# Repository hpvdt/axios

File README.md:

*This is the repository for our human powered submarine Axios, that we have decided to no longer to pursue. **IT IS NOT COMPLETE, LET ALONE TESTED.***

*Our motivation for making this repository public to to share what progress we did make to help others who might be interested in developing a similar system.*

# Axios

Our attempt at a human powered submarine, titled Axios. Within it there were two electronics systems to be implemented: rebreather monitoring and navigation. These were meant to be operate entirely independently of one another, being powered off separate batteries.

In this repository resides the code and hardware design files prepared for the initial versions of these systems from before the team decided to cancel the project.

Both systems were based around ATmega328P microcontrollers due to the team's familiarity with them and their adaquate amount of peripherals for serving both roles.

## Rebreather System

This was meant to supervise the different gas sensors around the submarine hull to inform the pilot about the atmospheric state within Axios. It collected data from three oxygen sensors and one carbon dioxide (CO2) sensor, it then displayed the value of each on separate seven-segment displays.

Of the two systems prepared for Axios, this was by far the more mature one. It was essentially ready for final deployment.

### Carbon Dioxide Sensing

For monitoring CO2 an MH-Z19 sensor was used which uses infrared to measure CO2 in the air. Getting data with the sensor was simple, it outputs a PWM signal at 1Hz that was trivial to monitor using the ATmega328P. The only hardware needed to interface it with the Arduino was a level shifting transistor to step the 3.3V PWM signal to 5V for the microcontroller to read.

One minor note we were unaware of is that the sensor has a small heater within it which is used to measure the CO2. This means the sensor occasionally draws a surge of current to keep it warm. This caused us to think the system was malfunctioning and drawing excessive power in our preliminary tests.

### Oxygen Sensing

This was the main focus of this board, since we were responsible for reading the raw sensor data. The oxygen sensors we were planning to use were standard oxygen sensors used for SCUBA diving. These are essentially chemical cells that when exposed to varying concentrations of oxygen in the air would vary their voltage proportionally. They had two issues the circuit needed to address:

1. The output voltage was pretty small. About 65mV for a new cell at 100% oxygen, but we would ideally be monitoring 21%, so about 20mV.
2. Although roughly linear, the output at 0% was not 0 mV, but about 15 mV.
3. Being chemical cells, they would gradually degrade and our circuit would need to be tuned for this.

The solution for this was a set of of high precision amplifiers made from operational amplifiers. These would buffer and then amplifier the sensor output to a level more easily read by the ATmega with its internal ADC resolution of about 4 mV. To adjust the circuit for the sensors as they aged we would conduct a two-point calibration (at 100% and 21% oxygen levels) adjusting potentiometers to get the display values to match these conditions.

## Navigation

Axios was designed to be controlled by three servo-actuated control fins. These needed a microcontroller to receive input from the captain (?) and actuate them accordingly. In addition to steering the submarine, it was planned for the captain of Axios to be provided orientation data about the submarine (roll, pitch, yaw), depth information, and power from their pedals. 

This board needs significant revision before it is worthy of installation into any submarine.

### Steering

Steering was to be done using a modified game controller (so we had wires directly to the potentiometers within it) which was read as an analog signal and then following some linear algebra, servo angles would be determined and set. Intentionally a short and simple loop.

There was discussion of a feature to have the submarine maintain depth without user input, but we never reached this stage.

### Orientation Data

Orientation data was meant to be provided by the use of a 9-axis IMU attached to the board. This approach quickly revealed a few key issues:

- The boards were going to move frequently within Axios, and the IMU would need to be calibrated for each new position. This could be remedied by off-boarding the IMU to a set location in Axios.
- The IMU only provided accelerations and magnetic field, we would need to code or find a library to perform the sensor fusion on the ATmega.
   - This would likely lead to significant usage of processor time
   - Our solution may not be able to replicate a more polished sensor even after significant work

Little was done for this as we were planning to transition to another IMU, the BNO055 which would address both of these points.

### Depth Information

Reading the depth was done using a pressure sensor that was connected to a port in the hull. The one we had acquired for Axios output a simple linear output proportional to the pressure sensed and a slight constant offset. Reading this analog signal, then dividing by the specific gravity of water would allow us to accurately estimate our depth in water.

### Pedal Power Data

This was planned to use a Raspberry Pi Zero with an ANT dongle to read available ANT data from the commercial power pedals in Axios and then broadcast it over UART to the microcontroller to display it for the rider.

This never really reached development, although it would likely be heavily based off the working ANT code prepared for [TITAN (2019)](https://github.com/hpvdt/titan_2019).

## Displays

The display system was identical across the boards. Given the amount of pins that needed to be controlled for all the displays a shift register was used for each display to control the segments as the digits were multiplexed by the microcontroller. This meant that all displays on a board could be controller by a handful of pins on the ATmega and a series of daisy-chained shift registers.

Although the two boards would operate separately, they were designed to be roughly arranged as shown below. These displays were meant to be bright enough to pass through the back of the partial mirror used to provide the captain a view.

# Software Used

For the design of the hardware EAGLE was used. For the microcontroller code it was all prepared using the Arduino IDE.

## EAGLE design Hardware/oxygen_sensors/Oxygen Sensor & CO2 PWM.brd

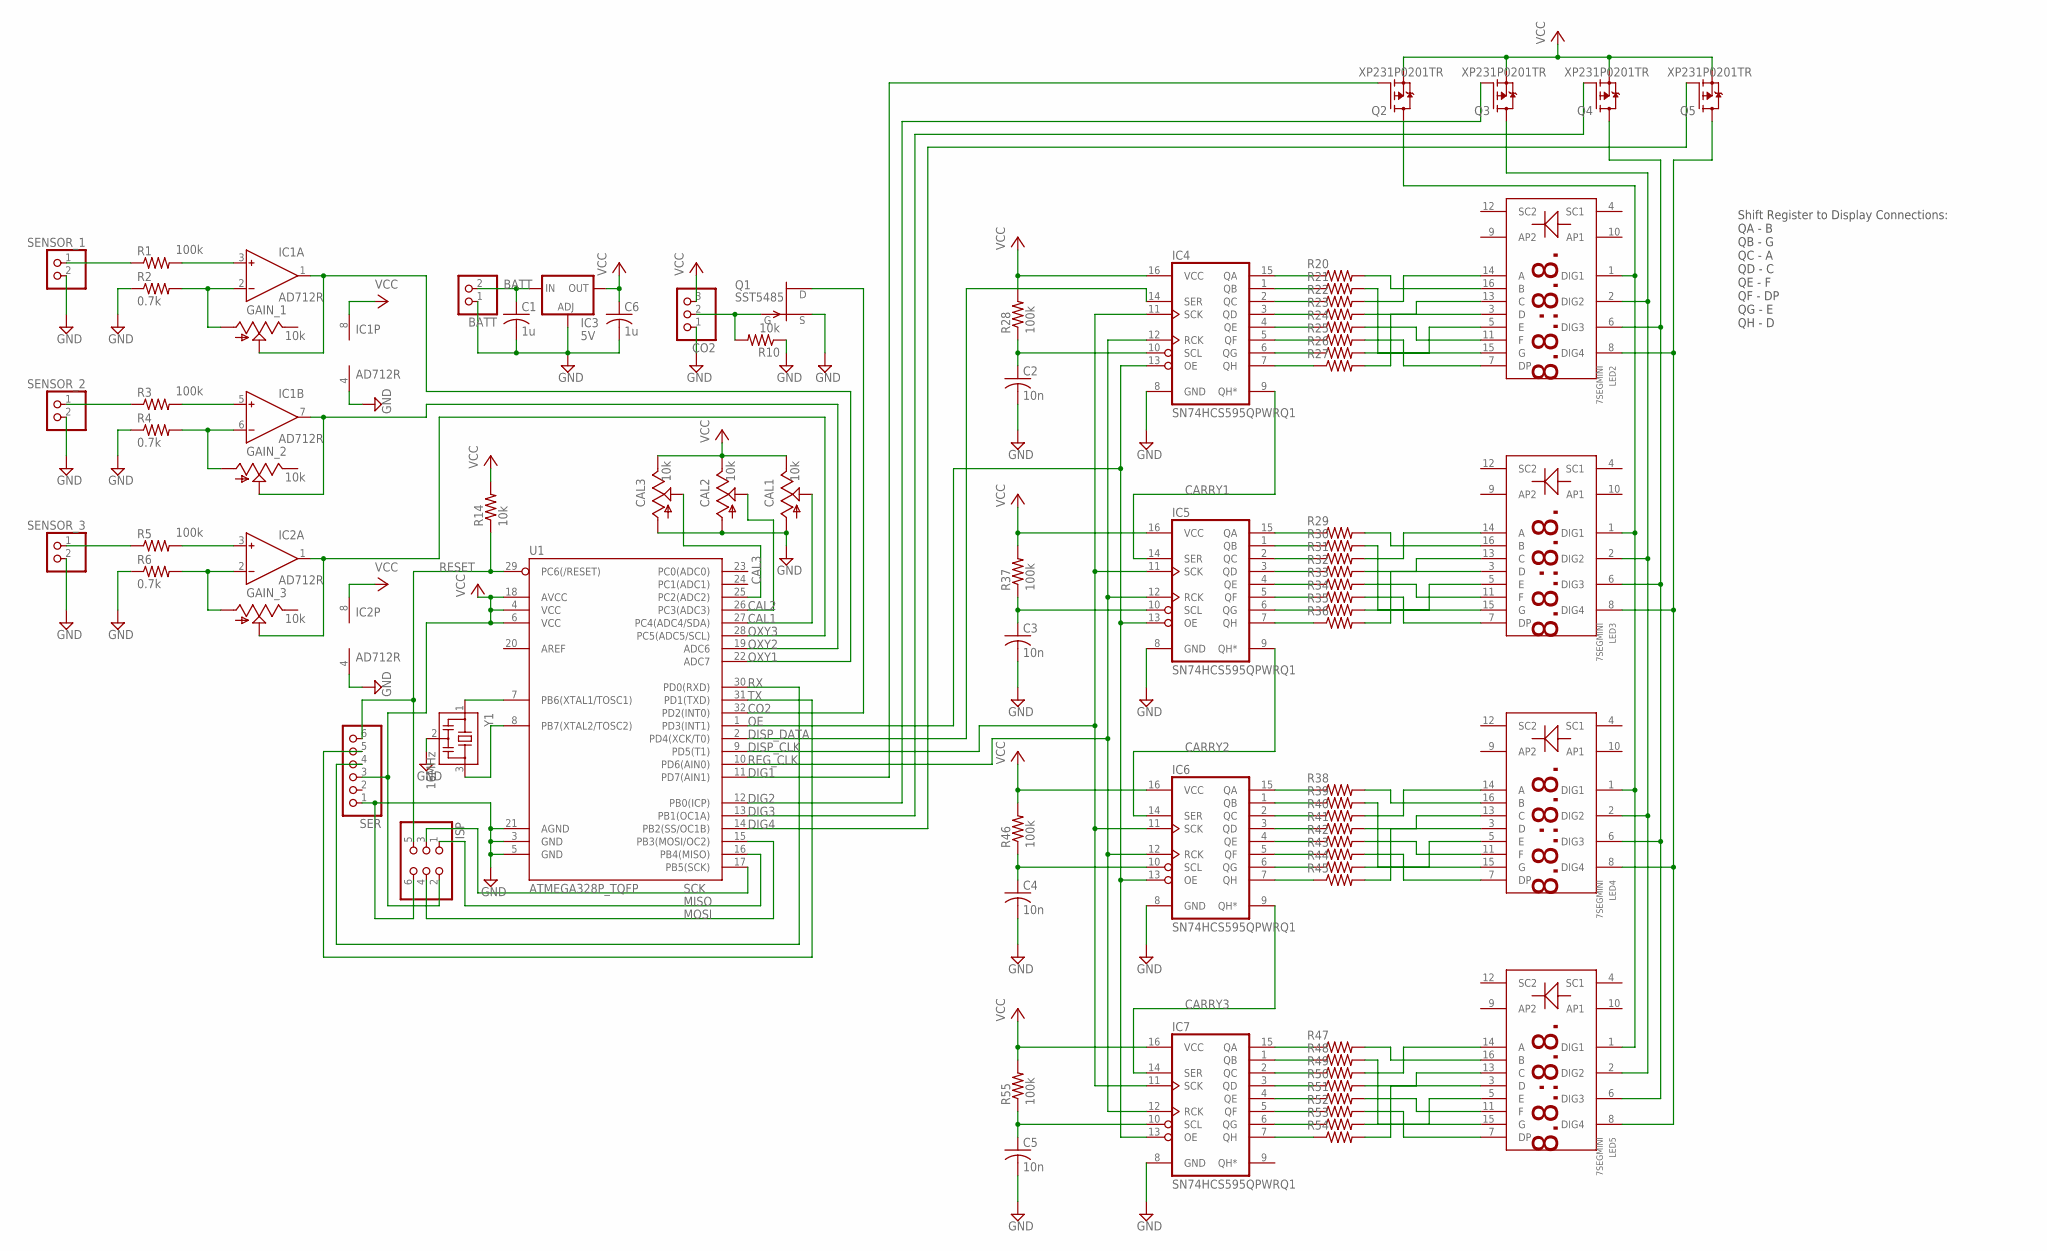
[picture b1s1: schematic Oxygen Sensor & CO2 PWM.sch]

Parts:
BATT: BATT; 1X02
C1, C6: 1u; C0603
C2, C3, C4, C5: 10n; C0603
CAL1, CAL2, CAL3: 10k; RJ9W
CO2: CO2; 1X03
GAIN_1, GAIN_2, GAIN_3: 10k; RJ9W
IC1, IC2: AD712R; SO8
IC3: 5V; SOT223
IC4, IC5, IC6, IC7: SN74HCS595QPWRQ1; TSSOP16
ISP: ISP; 2X03
LED2, LED3, LED4, LED5: 7SEGMINI
Q1: SST5485; SOT23
Q2, Q3, Q4, Q5: XP231P0201TR; SOT23
R1, R3, R5, R28, R37, R46, R55: 100k; R0603
R2, R4, R6: 0.7k; R0603
R10, R14: 10k; R0603
R20, R21, R22, R23, R24, R25, R26, R27, R29, R30, R31, R32, R33, R34, R35, R36, R38, R39, R40, R41, R42, R43, R44, R45, R47, R48, R49, R50, R51, R52, R53, R54: R-US_R0603; R0603
SENSOR_1, SENSOR_2, SENSOR_3: PINHD-1X2; 1X02
SER: SER; 1X06
U1: ATMEGA328P_TQFP; TQFP32-08
Y1: 16MHz; CSTCR6M

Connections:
BATT: BATT.2, C1.1, IC3.3 (IN)
CAL1: CAL1.S, U1.27 (PC4(ADC4/SDA))
CAL2: CAL2.S, U1.26 (PC3(ADC3))
CAL3: CAL3.S, U1.25 (PC2(ADC2))
CARRY1: IC4.9 (QH*), IC5.14 (SER)
CARRY2: IC5.9 (QH*), IC6.14 (SER)
CARRY3: IC6.9 (QH*), IC7.14 (SER)
CO2: Q1.1 (D), U1.32 (PD2(INT0))
CO2_PWM: CO2.2, Q1.3 (G), R10.2
COM_D1: LED2.1 (DIG1), LED3.1 (DIG1), LED4.1 (DIG1), LED5.1 (DIG1), Q2.3 (D)
COM_D2: LED2.2 (DIG2), LED3.2 (DIG2), LED4.2 (DIG2), LED5.2 (DIG2), Q3.3 (D)
COM_D3: LED2.6 (DIG3), LED3.6 (DIG3), LED4.6 (DIG3), LED5.6 (DIG3), Q4.3 (D)
COM_D4: LED2.8 (DIG4), LED3.8 (DIG4), LED4.8 (DIG4), LED5.8 (DIG4), Q5.3 (D)
DIG1: Q2.1 (G), U1.11 (PD7(AIN1))
DIG2: Q3.1 (G), U1.12 (PB0(ICP))
DIG3: Q4.1 (G), U1.13 (PB1(OC1A))
DIG4: Q5.1 (G), U1.14 (PB2(SS/OC1B))
DISP_CLK: IC4.11 (SCK), IC5.11 (SCK), IC6.11 (SCK), IC7.11 (SCK), U1.9 (PD5(T1))
DISP_DATA: IC4.14 (SER), U1.2 (PD4(XCK/T0))
GND: BATT.1, C1.2, C2.2, C3.2, C4.2, C5.2, C6.2, CAL1.A, CAL2.A, CAL3.A, CO2.1, IC1.4 (V-), IC2.4 (V-), IC3.1 (ADJ), IC4.8 (GND), IC5.8 (GND), IC6.8 (GND), IC7.8 (GND), ISP.6, Q1.2 (S), R2.1, R4.1, R6.1, R10.1, SENSOR_1.2, SENSOR_2.2, SENSOR_3.2, SER.1, U1.3 (GND), U1.5 (GND), U1.21 (AGND), Y1.2
MISO: ISP.1, U1.16 (PB4(MISO))
MOSI: ISP.4, U1.15 (PB3(MOSI/OC2))
unnamed: IC1.3 (IN+), R1.2
unnamed: GAIN_1.A, IC1.2 (IN-), R2.2
unnamed: IC1.5 (IN+), R3.2
unnamed: GAIN_2.A, IC1.6 (IN-), R4.2
unnamed: IC2.3 (IN+), R5.2
unnamed: GAIN_3.A, IC2.2 (IN-), R6.2
unnamed: U1.7 (PB6(XTAL1/TOSC1)), Y1.1
unnamed: U1.8 (PB7(XTAL2/TOSC2)), Y1.3
unnamed: IC4.15 (QA), R20.1
unnamed: IC4.1 (QB), R21.1
unnamed: IC4.2 (QC), R22.1
unnamed: IC4.3 (QD), R23.1
unnamed: IC4.4 (QE), R24.1
unnamed: IC4.5 (QF), R25.1
unnamed: IC4.6 (QG), R26.1
unnamed: IC4.7 (QH), R27.1
unnamed: C2.1, IC4.10 (SCL), R28.1
unnamed: LED2.16 (B), R20.2
unnamed: LED2.15 (G), R21.2
unnamed: LED2.14 (A), R22.2
unnamed: LED2.13 (C), R23.2
unnamed: LED2.11 (F), R24.2
unnamed: LED2.7 (DP), R25.2
unnamed: LED2.5 (E), R26.2
unnamed: LED2.3 (D), R27.2
unnamed: IC5.15 (QA), R29.1
unnamed: IC5.1 (QB), R30.1
unnamed: IC5.2 (QC), R31.1
unnamed: IC5.3 (QD), R32.1
unnamed: IC5.4 (QE), R33.1
unnamed: IC5.5 (QF), R34.1
unnamed: IC5.6 (QG), R35.1
unnamed: IC5.7 (QH), R36.1
unnamed: C3.1, IC5.10 (SCL), R37.1
unnamed: LED3.16 (B), R29.2
unnamed: LED3.15 (G), R30.2
unnamed: LED3.14 (A), R31.2
unnamed: LED3.13 (C), R32.2
unnamed: LED3.11 (F), R33.2
unnamed: LED3.7 (DP), R34.2
unnamed: LED3.5 (E), R35.2
unnamed: LED3.3 (D), R36.2
unnamed: IC6.15 (QA), R38.1
unnamed: IC6.1 (QB), R39.1
unnamed: IC6.2 (QC), R40.1
unnamed: IC6.3 (QD), R41.1
unnamed: IC6.4 (QE), R42.1
unnamed: IC6.5 (QF), R43.1
unnamed: IC6.6 (QG), R44.1
unnamed: IC6.7 (QH), R45.1
unnamed: C4.1, IC6.10 (SCL), R46.1
unnamed: LED4.16 (B), R38.2
unnamed: LED4.15 (G), R39.2
unnamed: LED4.14 (A), R40.2
unnamed: LED4.13 (C), R41.2
unnamed: LED4.11 (F), R42.2
unnamed: LED4.7 (DP), R43.2
unnamed: LED4.5 (E), R44.2
unnamed: LED4.3 (D), R45.2
unnamed: IC7.15 (QA), R47.1
unnamed: IC7.1 (QB), R48.1
unnamed: IC7.2 (QC), R49.1
unnamed: IC7.3 (QD), R50.1
unnamed: IC7.4 (QE), R51.1
unnamed: IC7.5 (QF), R52.1
unnamed: IC7.6 (QG), R53.1
unnamed: IC7.7 (QH), R54.1
unnamed: C5.1, IC7.10 (SCL), R55.1
unnamed: LED5.16 (B), R47.2
unnamed: LED5.15 (G), R48.2
unnamed: LED5.14 (A), R49.2
unnamed: LED5.13 (C), R50.2
unnamed: LED5.11 (F), R51.2
unnamed: LED5.7 (DP), R52.2
unnamed: LED5.5 (E), R53.2
unnamed: LED5.3 (D), R54.2
O2SENS_1: R1.1, SENSOR_1.1
O2SENS_2: R3.1, SENSOR_2.1
O2SENS_3: R5.1, SENSOR_3.1
OE: IC4.13 (OE), IC5.13 (OE), IC6.13 (OE), IC7.13 (OE), U1.1 (PD3(INT1))
OXY1: GAIN_1.S, IC1.1 (OUT), U1.22 (ADC7)
OXY2: GAIN_2.S, IC1.7 (OUT), U1.19 (ADC6)
OXY3: GAIN_3.S, IC2.1 (OUT), U1.28 (PC5(ADC5/SCL))
REG_CLK: IC4.12 (RCK), IC5.12 (RCK), IC6.12 (RCK), IC7.12 (RCK), U1.10 (PD6(AIN0))
RESET: ISP.5, R14.1, SER.6, U1.29 (PC6(/RESET))
RX: SER.4, U1.30 (PD0(RXD))
SCK: ISP.3, U1.17 (PB5(SCK))
TX: SER.5, U1.31 (PD1(TXD))
VCC: C6.1, CAL1.E, CAL2.E, CAL3.E, CO2.3, IC1.8 (V+), IC2.8 (V+), IC3.4 (OUT), IC4.16 (VCC), IC5.16 (VCC), IC6.16 (VCC), IC7.16 (VCC), ISP.2, Q2.2 (S), Q3.2 (S), Q4.2 (S), Q5.2 (S), R14.2, R28.2, R37.2, R46.2, R55.2, SER.3, U1.4 (VCC), U1.6 (VCC), U1.18 (AVCC)

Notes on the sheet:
Shift Register to Display Connections: QA - B QB - G QC - A QD - C QE - F QF - DP QG - E QH - D

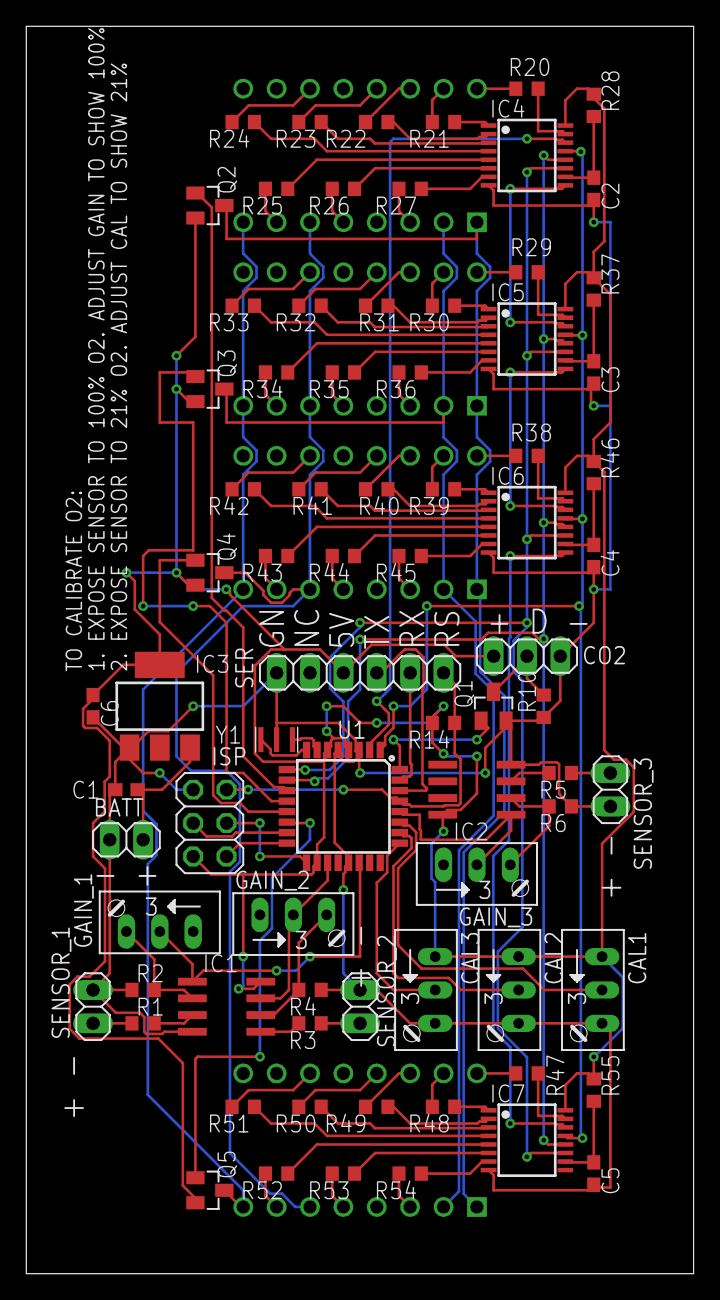
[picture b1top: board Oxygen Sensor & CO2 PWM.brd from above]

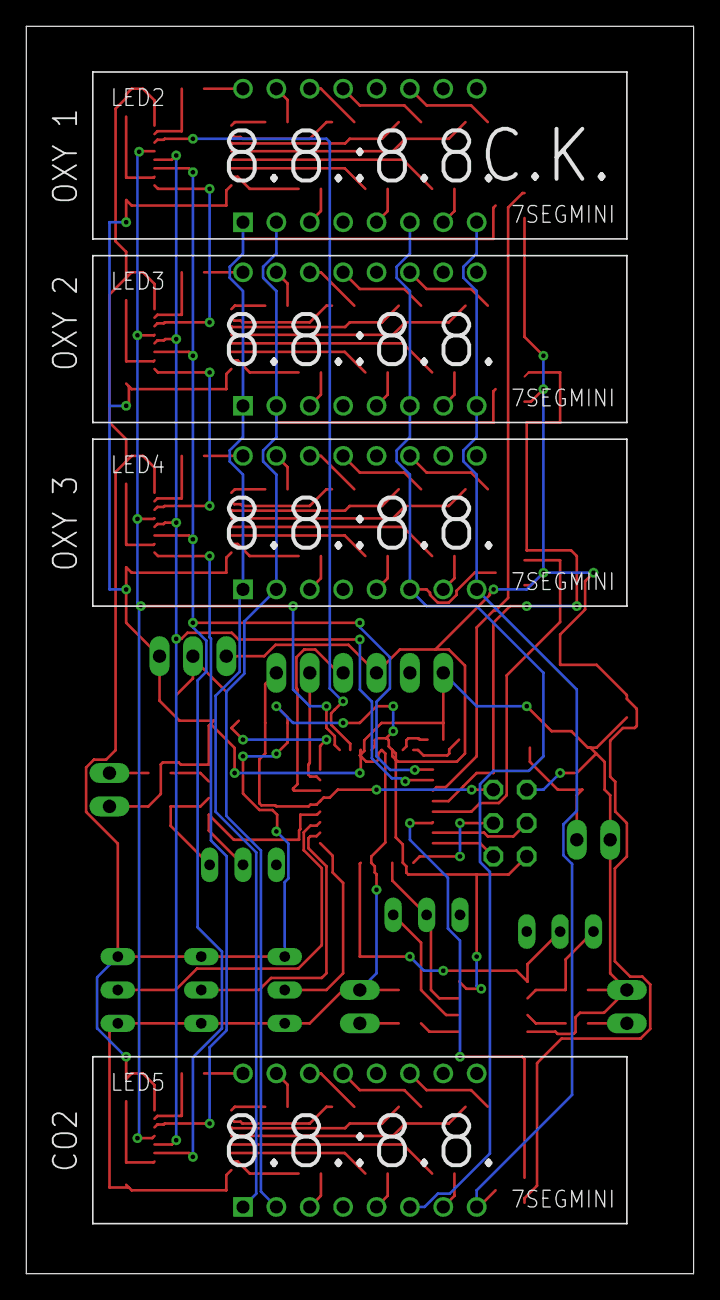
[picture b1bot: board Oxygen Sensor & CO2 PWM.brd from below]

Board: 2 copper layers, 50.8 x 94.9 mm, 81 parts (4 on the bottom side), 111 nets.

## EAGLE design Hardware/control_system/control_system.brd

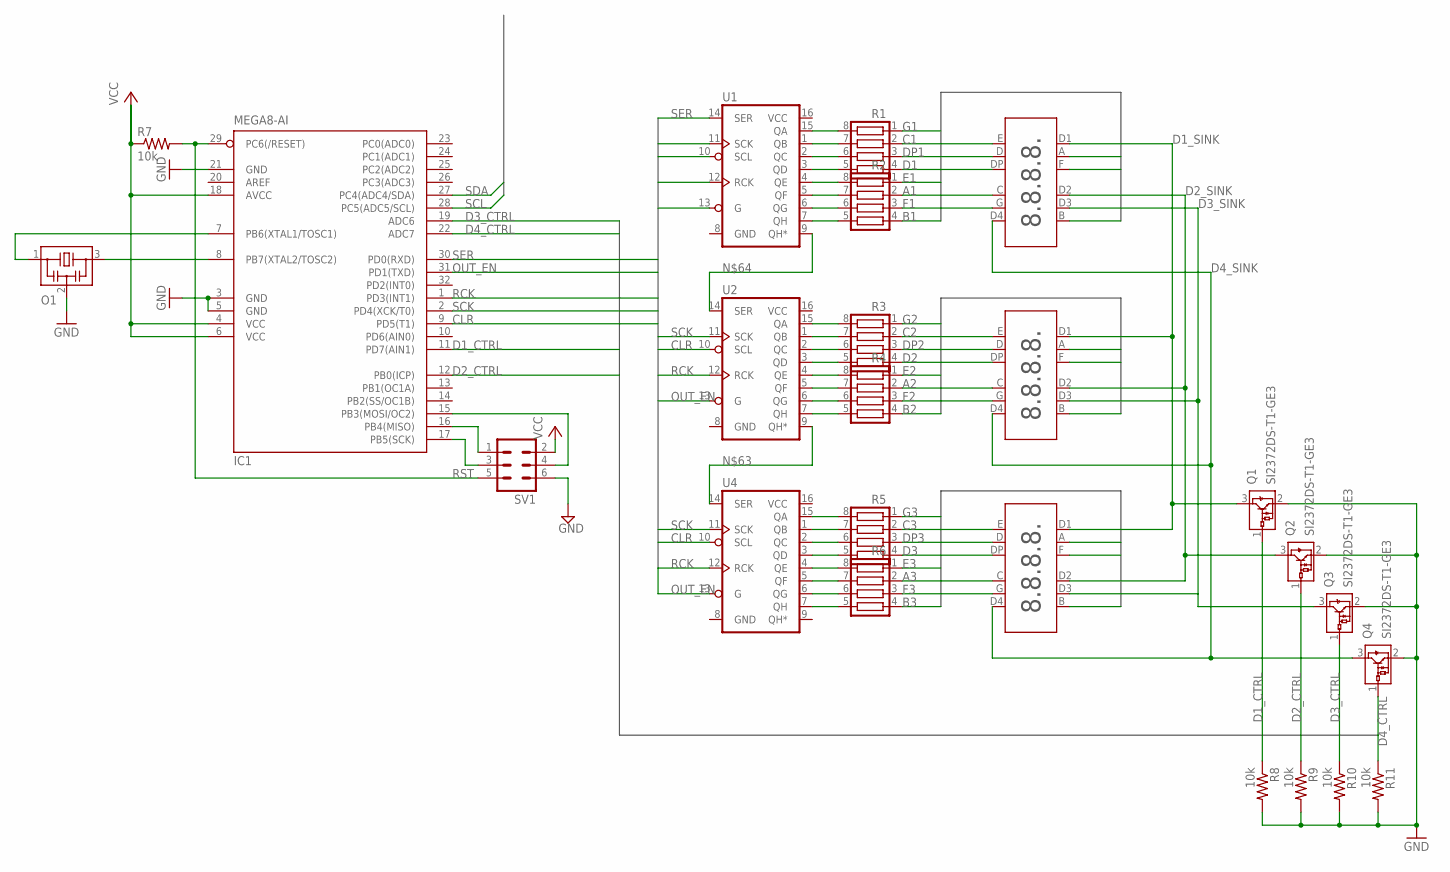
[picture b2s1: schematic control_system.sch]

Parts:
IC1: MEGA8-AI; TQFP32-08
LED1, LED2, LED3: 7SEG20MM
O1: CSTNE16M0V530000R0; CSTCR6M
Q1, Q2, Q3, Q4: SI2372DS-T1-GE3; SOT23
R1, R2, R3, R4, R5, R6: 220; RESCAXS50P200X150X50-8N
R7, R8, R9, R10, R11: 10k; R0402
SV1: MA03-2
U1, U2, U4: 74595; TSSOP16

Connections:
A1: LED1.A, R2.2
A2: LED2.A, R4.2
A3: LED3.A, R6.2
B1: LED1.B, R2.4
B2: LED2.B, R4.4
B3: LED3.B, R6.4
C1: LED1.C, R1.2
C2: LED2.C, R3.2
C3: LED3.C, R5.2
CLR: IC1.9 (PD5(T1)), U1.10 (SCL), U2.10 (SCL), U4.10 (SCL)
D1: LED1.D, R1.4
D1_CTRL: IC1.11 (PD7(AIN1)), Q1.1 (VIN), R8.1
D1_SINK: LED1.D1, LED2.D1, LED3.D1, Q1.3 (VOUT)
D2: LED2.D, R3.4
D2_CTRL: IC1.12 (PB0(ICP)), Q2.1 (VIN), R9.1
D2_SINK: LED1.D2, LED2.D2, LED3.D2, Q2.3 (VOUT)
D3: LED3.D, R5.4
D3_CTRL: IC1.19 (ADC6), Q3.1 (VIN), R10.1
D3_SINK: LED1.D3, LED2.D3, LED3.D3, Q3.3 (VOUT)
D4_CTRL: IC1.22 (ADC7), Q4.1 (VIN), R11.1
D4_SINK: LED1.D4, LED2.D4, LED3.D4, Q4.3 (VOUT)
DP1: LED1.DP, R1.3
DP2: LED2.DP, R3.3
DP3: LED3.DP, R5.3
E1: LED1.E, R2.1
E2: LED2.E, R4.1
E3: LED3.E, R6.1
F1: LED1.F, R2.3
F2: LED2.F, R4.3
F3: LED3.F, R6.3
G1: LED1.G, R1.1
G2: LED2.G, R3.1
G3: LED3.G, R5.1
GND: IC1.3 (GND), IC1.5 (GND), IC1.21 (GND), O1.2, Q1.2 (GND), Q2.2 (GND), Q3.2 (GND), Q4.2 (GND), R8.2, R9.2, R10.2, R11.2, SV1.6, U1.8 (GND), U2.8 (GND), U4.8 (GND)
MISO: IC1.16 (PB4(MISO)), SV1.1
MOSI: IC1.15 (PB3(MOSI/OC2)), SV1.4
unnamed: R1.8, U1.15 (QA)
unnamed: R1.7, U1.1 (QB)
unnamed: R1.6, U1.2 (QC)
unnamed: R1.5, U1.3 (QD)
unnamed: R2.8, U1.4 (QE)
unnamed: R2.7, U1.5 (QF)
unnamed: R2.6, U1.6 (QG)
unnamed: R2.5, U1.7 (QH)
unnamed: IC1.7 (PB6(XTAL1/TOSC1)), O1.1
unnamed: IC1.8 (PB7(XTAL2/TOSC2)), O1.3
unnamed: R3.8, U2.15 (QA)
unnamed: R3.7, U2.1 (QB)
unnamed: R3.6, U2.2 (QC)
unnamed: R3.5, U2.3 (QD)
unnamed: R4.8, U2.4 (QE)
unnamed: R4.7, U2.5 (QF)
unnamed: R4.6, U2.6 (QG)
unnamed: R4.5, U2.7 (QH)
unnamed: R5.8, U4.15 (QA)
unnamed: R5.7, U4.1 (QB)
unnamed: R5.6, U4.2 (QC)
unnamed: R5.5, U4.3 (QD)
unnamed: R6.8, U4.4 (QE)
unnamed: R6.7, U4.5 (QF)
unnamed: R6.6, U4.6 (QG)
unnamed: R6.5, U4.7 (QH)
unnamed: U2.9 (QH*), U4.14 (SER)
unnamed: U1.9 (QH*), U2.14 (SER)
OUT_EN: IC1.31 (PD1(TXD)), U1.13 (G), U2.13 (G), U4.13 (G)
RCK: IC1.1 (PD3(INT1)), U1.12 (RCK), U2.12 (RCK), U4.12 (RCK)
RST: IC1.29 (PC6(/RESET)), R7.2, SV1.5
SCK: IC1.2 (PD4(XCK/T0)), U1.11 (SCK), U2.11 (SCK), U4.11 (SCK)
SCK1: IC1.17 (PB5(SCK)), SV1.3
SCL: IC1.28 (PC5(ADC5/SCL))
SDA: IC1.27 (PC4(ADC4/SDA))
SER: IC1.30 (PD0(RXD)), U1.14 (SER)
VCC: IC1.4 (VCC), IC1.6 (VCC), IC1.18 (AVCC), R7.1, SV1.2, U1.16 (VCC), U2.16 (VCC), U4.16 (VCC)

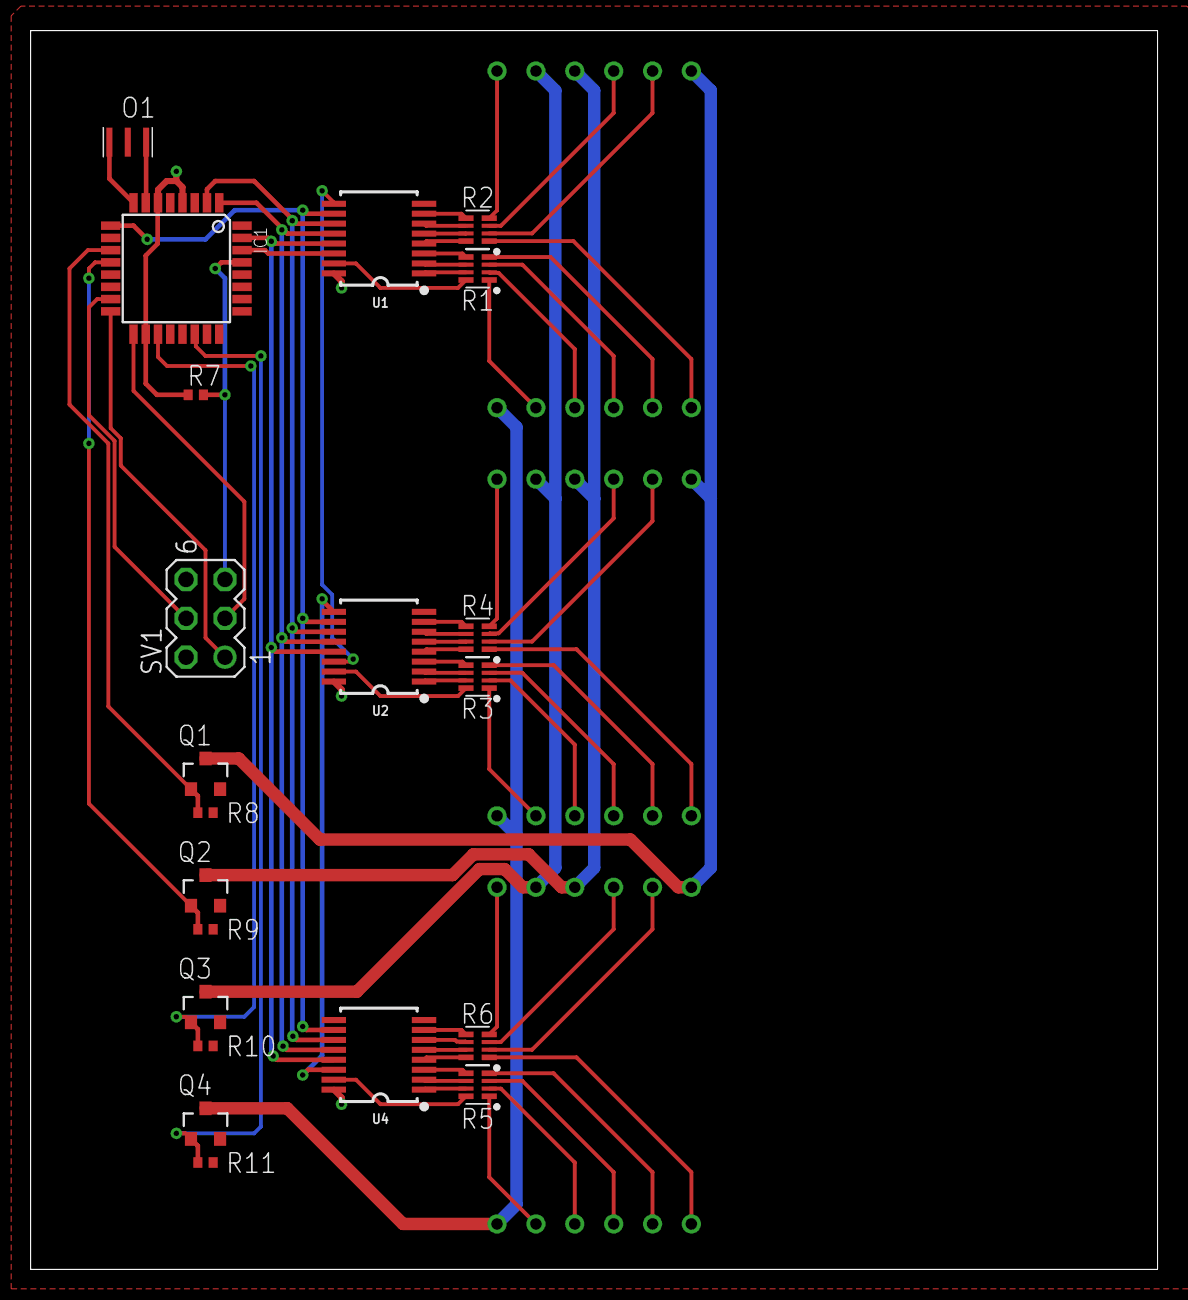
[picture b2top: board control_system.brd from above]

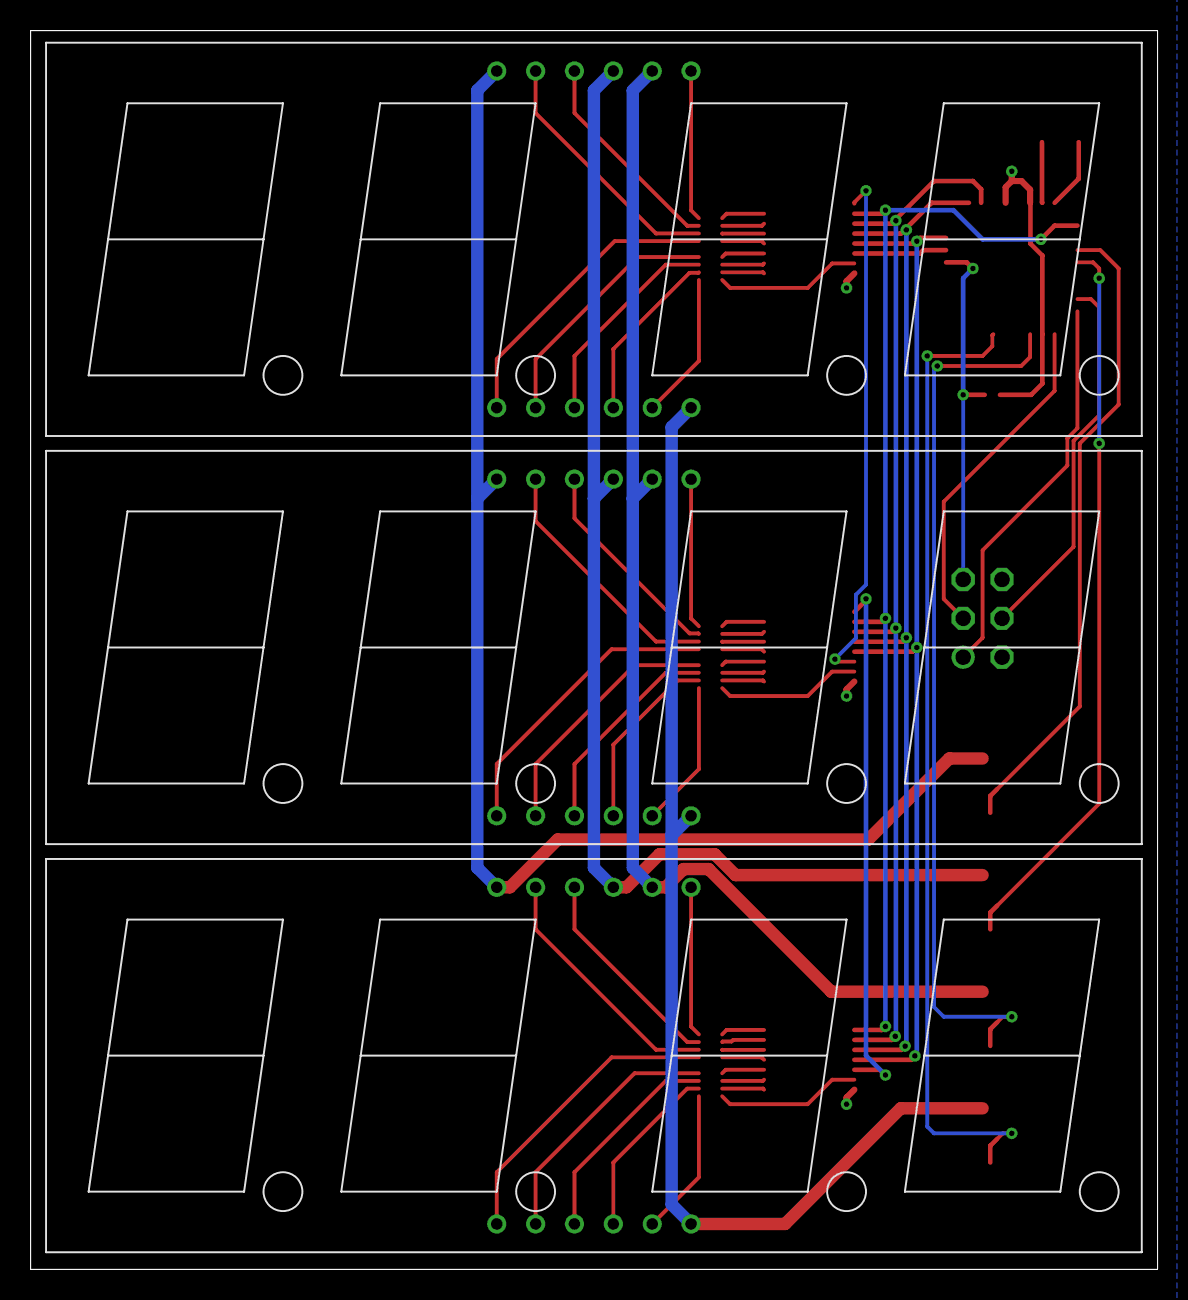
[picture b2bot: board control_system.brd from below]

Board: 2 copper layers, 73.6 x 81.0 mm, 24 parts (3 on the bottom side), 71 nets.

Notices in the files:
parts and their libraries:
diy-modules: Released under the Creative Commons Attribution 4.0 International License: http://creativecommons.org/licenses/by/4.0
SparkFun-IC-Logic: Licensing: Creative Commons ShareAlike 4.0 International - https://creativecommons.org/licenses/by-sa/4.0
